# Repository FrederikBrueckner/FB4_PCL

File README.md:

# FB4_PCL
### FH Aachen FB4 Physical Computing Lab Repository

#### Arduino

To get started with Arduino, download the Arduino IDE from the [Arduino download site](https://www.arduino.cc/en/Main/Software)

Check out the Arduino reference. It is very comprehensive :)
[Arduino IDE reference](https://www.arduino.cc/reference/en/)

If you want to really dive into the coding world and explore all the amazing possibilities, check out the Eclipse IDE and Sloeber plugin!

[Eclipse IDE](https://www.eclipse.org/)

[Arduino plugin for Eclipse IDE](http://eclipse.baeyens.it/)

In case Eclipse fails to install under OS X because Java VM needs to be updated: [How to update Java with homebrew](http://www.lonecpluspluscoder.com/2017/04/27/installing-java-8-jdk-os-x-using-homebrew/)

#### Processing

To get started with Processing, download the Processing IDE from the [Processing download site](https://processing.org/download/)

Tutorials and demo sketches as entry points:

[Processing tutorials](https://processing.org/tutorials/)

[OpenProcessing.org projects](https://www.openprocessing.org/browse/)

Here are some pointers for setting up [Processing in Eclipse](https://www.processing.org/tutorials/eclipse/)

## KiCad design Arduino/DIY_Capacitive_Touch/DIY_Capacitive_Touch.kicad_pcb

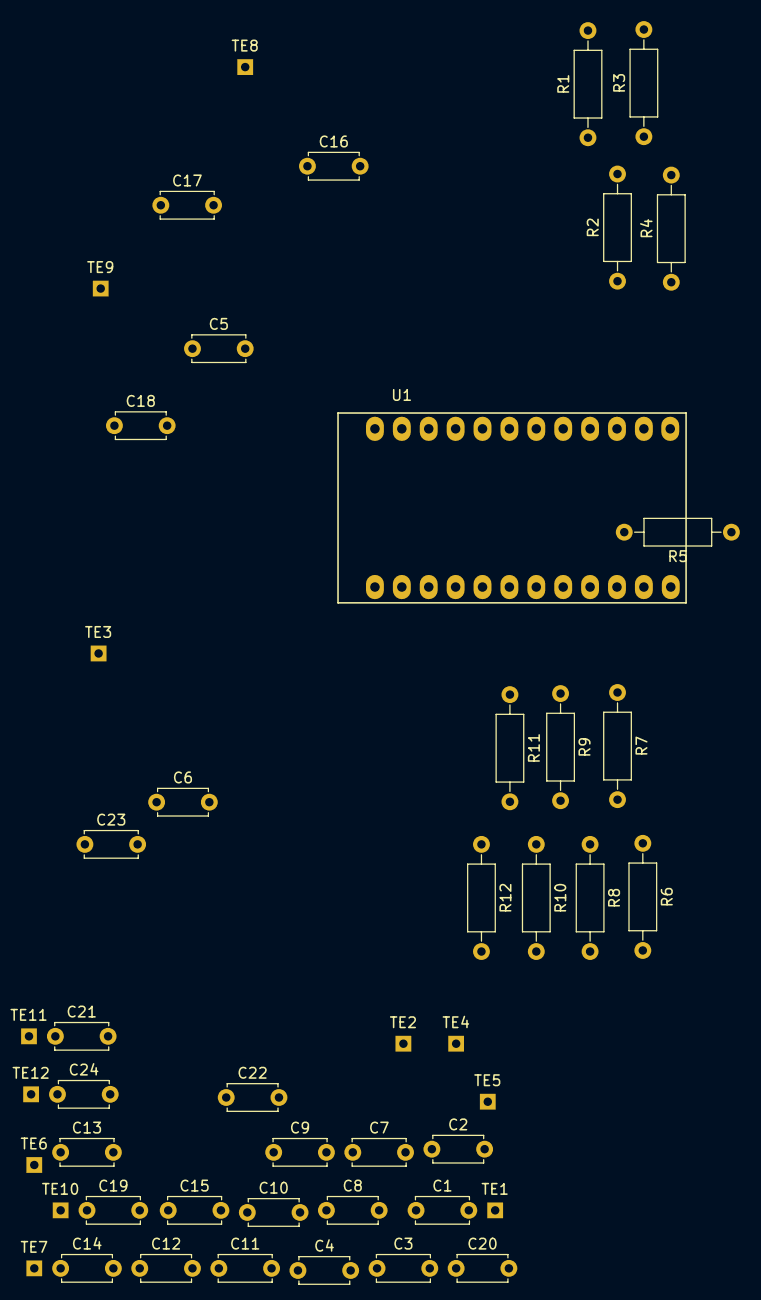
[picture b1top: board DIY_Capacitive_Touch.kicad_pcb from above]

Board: 2 copper layers, 49 parts (0 on the bottom side), 26 nets, no tracks yet.

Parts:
C1, C3, C5, C7, C9, C11, C13, C15, C17, C19, C21, C23: 180pF; C_Disc_D5.0mm_W2.5mm_P5.00mm
C2, C4, C6, C8, C10, C12, C14, C16, C18, C20, C22, C24: 100pF; C_Disc_D4.7mm_W2.5mm_P5.00mm
R1, R2, R3, R4, R5, R6, R7, R8, R9, R10, R11, R12: 1mΩ; R_Axial_DIN0207_L6.3mm_D2.5mm_P10.16mm_Horizontal
TE1, TE2, TE3, TE4, TE5, TE6, TE7, TE8, TE9, TE10, TE11, TE12: Electrode; Measurement_Point_Square-TH_Small
U1: Arduino_Pro_Micro

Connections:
GNDREF: C2.2, C4.2, C6.2, C8.2, C10.2, C12.2, C14.2, C16.2, C18.2, C20.2, C22.2, C24.2
unnamed: C1.1, C2.1, TE1.1
unnamed: C1.2, R1.1, U1.15
unnamed: C3.1, C4.1, TE2.1
unnamed: C3.2, R2.1, U1.14
unnamed: C5.1, C6.1, TE3.1
unnamed: C5.2, R3.1, U1.16
unnamed: C7.1, C8.1, TE4.1
unnamed: C7.2, R4.1, U1.10
unnamed: C9.2, R5.1, U1.9
unnamed: C9.1, C10.1, TE5.1
unnamed: C11.1, C12.1, TE6.1
unnamed: C11.2, R6.1, U1.8
unnamed: C13.1, C14.1, TE7.1
unnamed: C13.2, R7.1, U1.7
unnamed: C15.1, C16.1, TE8.1
unnamed: C15.2, R8.1, U1.6
unnamed: C17.1, C18.1, TE9.1
unnamed: C17.2, R9.1, U1.5
unnamed: C19.1, C20.1, TE10.1
unnamed: C19.2, R10.1, U1.4
unnamed: C21.1, C22.1, TE11.1
unnamed: C21.2, R11.1, U1.3
unnamed: C23.1, C24.1, TE12.1
unnamed: C23.2, R12.1, U1.2
unnamed: R1.2, R2.2, R3.2, R4.2, R5.2, R6.2, R7.2, R8.2, R9.2, R10.2, R11.2, R12.2

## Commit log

2017-11-19 initial commit
    Leonardo based HID with joystick, rotary encoders, buttons and simple
    LED display
2017-11-19 libraries added, markup
    Added libraries by Buxtronix and Avishorp
2017-11-19 Prototype 2017-11-19
2017-11-19 Markup + documentation
2017-11-19 Rename README.MD to README.md
2017-11-20 Formating
2017-11-23 MPR121 demo
2017-11-26 Tools added
2017-12-13 Poti_Mouse sketch added
    Arduino sketch to map potentiometers to move mouse cursor to absolute
    screen positions
2017-12-13 fix Errors
2017-12-15 Syntax
2017-12-17 Update description, add picture
2017-12-17 comments added
2017-12-17 Documentation on PWM frequency prescaler
2017-12-18 Information update
2017-12-18 Multi press button fade - initial commit
2017-12-18 Bugfix
2017-12-18 Diamix Prog-S2 info
2017-12-20 Single click on/off, double + triple click detection
2017-12-20 Change SVG colors with mouse move
2017-12-20 MPR121_MP3Player added
2017-12-21 Ultrasonic distance initial commit
2017-12-22 Distance zone handling added
2018-01-02 Basic schematic added
2018-01-11 Firmware rewrite
2018-01-11 Five sensors with median filtering
    50ms delay between sensor switch to clean up noise floor
2018-01-14 Added capacitive touch
2018-01-14 Reorganize file structure
2018-01-14 Schematic
2018-01-15 Update capacitive touch
2018-01-16 Typo
2018-01-16 Only print different keys
2018-01-17 Added playlist functionality
2018-01-22 Change button behavior
    Count button presses and fade through levels instead of double click
    behavior
2018-01-22 Code clean up and annotation
2018-01-31 Update fade behavior
2018-02-04 MPR121 debug messages
2018-02-04 MPR121 bugfix
2018-02-04 MPR121 bugfix
    Record mode behavior fix
2018-02-05 MPR121 debugging
2018-02-06 Record mode bugfix
2018-02-08 Ultrasonic sensor array distance
2018-02-09 MPR121 variable length mismatch?
2018-03-13 Tinkerbox1 update
2018-05-16 Processing EyeTracking Demo
2018-05-16 Processing_readfromFile
2018-05-16 Data_transform_Sketch
2018-05-16 Update_EyeTrackTrail
2018-05-23 update comments
2018-05-29 Ten touch sensors keypress
2018-05-30 minor bugfix
2018-07-04 MPR121 Keyboard Sketch
2018-07-04 Tinkerbox with additional switch
2018-07-17 Sketch for five button exhibition interface
    Five buttons and a doppler radar sensor to activate the display via
    processing.
2018-12-19 Dimmer_Edit_Peter_Johannes
2018-12-19 Various
2019-01-03 Two button interface sketch stub
2019-01-10 Bugfixes, keyboard only
2019-01-16 Capacitive plate dimmer code added
2019-01-16 NoNameLight
2019-01-17 UX belt base sketch
2019-01-23 Bugfixes
2019-01-23 On/Off timer added
2019-01-27 A ton of bugfixes. :)
2019-01-30 bugfix touch
2019-01-30 Account for reference values
2019-05-22 AR Marker Test
2019-06-26 Create Einklang.ino
    Simple 3 potentiometer interface
2019-06-26 Test
2019-06-26 Serial_Event listener added
2019-07-03 Einklang sketch updates
2019-07-03 Code defragmentation and clean up
2019-07-03 Filename correction
2019-07-03 Cleanup
    Deleting file doublets
2019-07-03 Split for better overview of code
2019-07-03 Sounds not playing, needs fix.
2019-07-03 Performance fixes, sound still broken
2019-07-03 Code cleanup
2019-07-03 Audio Fix. :)
2019-07-03 FFT / Dots fix
2019-12-11 Added soft latch power toggle schematic
2019-12-13 Clean_up
2020-01-08 Added dimmer functionality
2020-01-08 Added comments
